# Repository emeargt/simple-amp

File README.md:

# simple-amp
This repository contains a KiCad project for a simple guitar bridge amplifier.

The board is designed to fit in a stomp box with panel mount switches.

## Schematic

## Board Layout
Top | Bottom
:---: | :---:
 | 

## Changelog

### v01
* Initial schematic and board layout

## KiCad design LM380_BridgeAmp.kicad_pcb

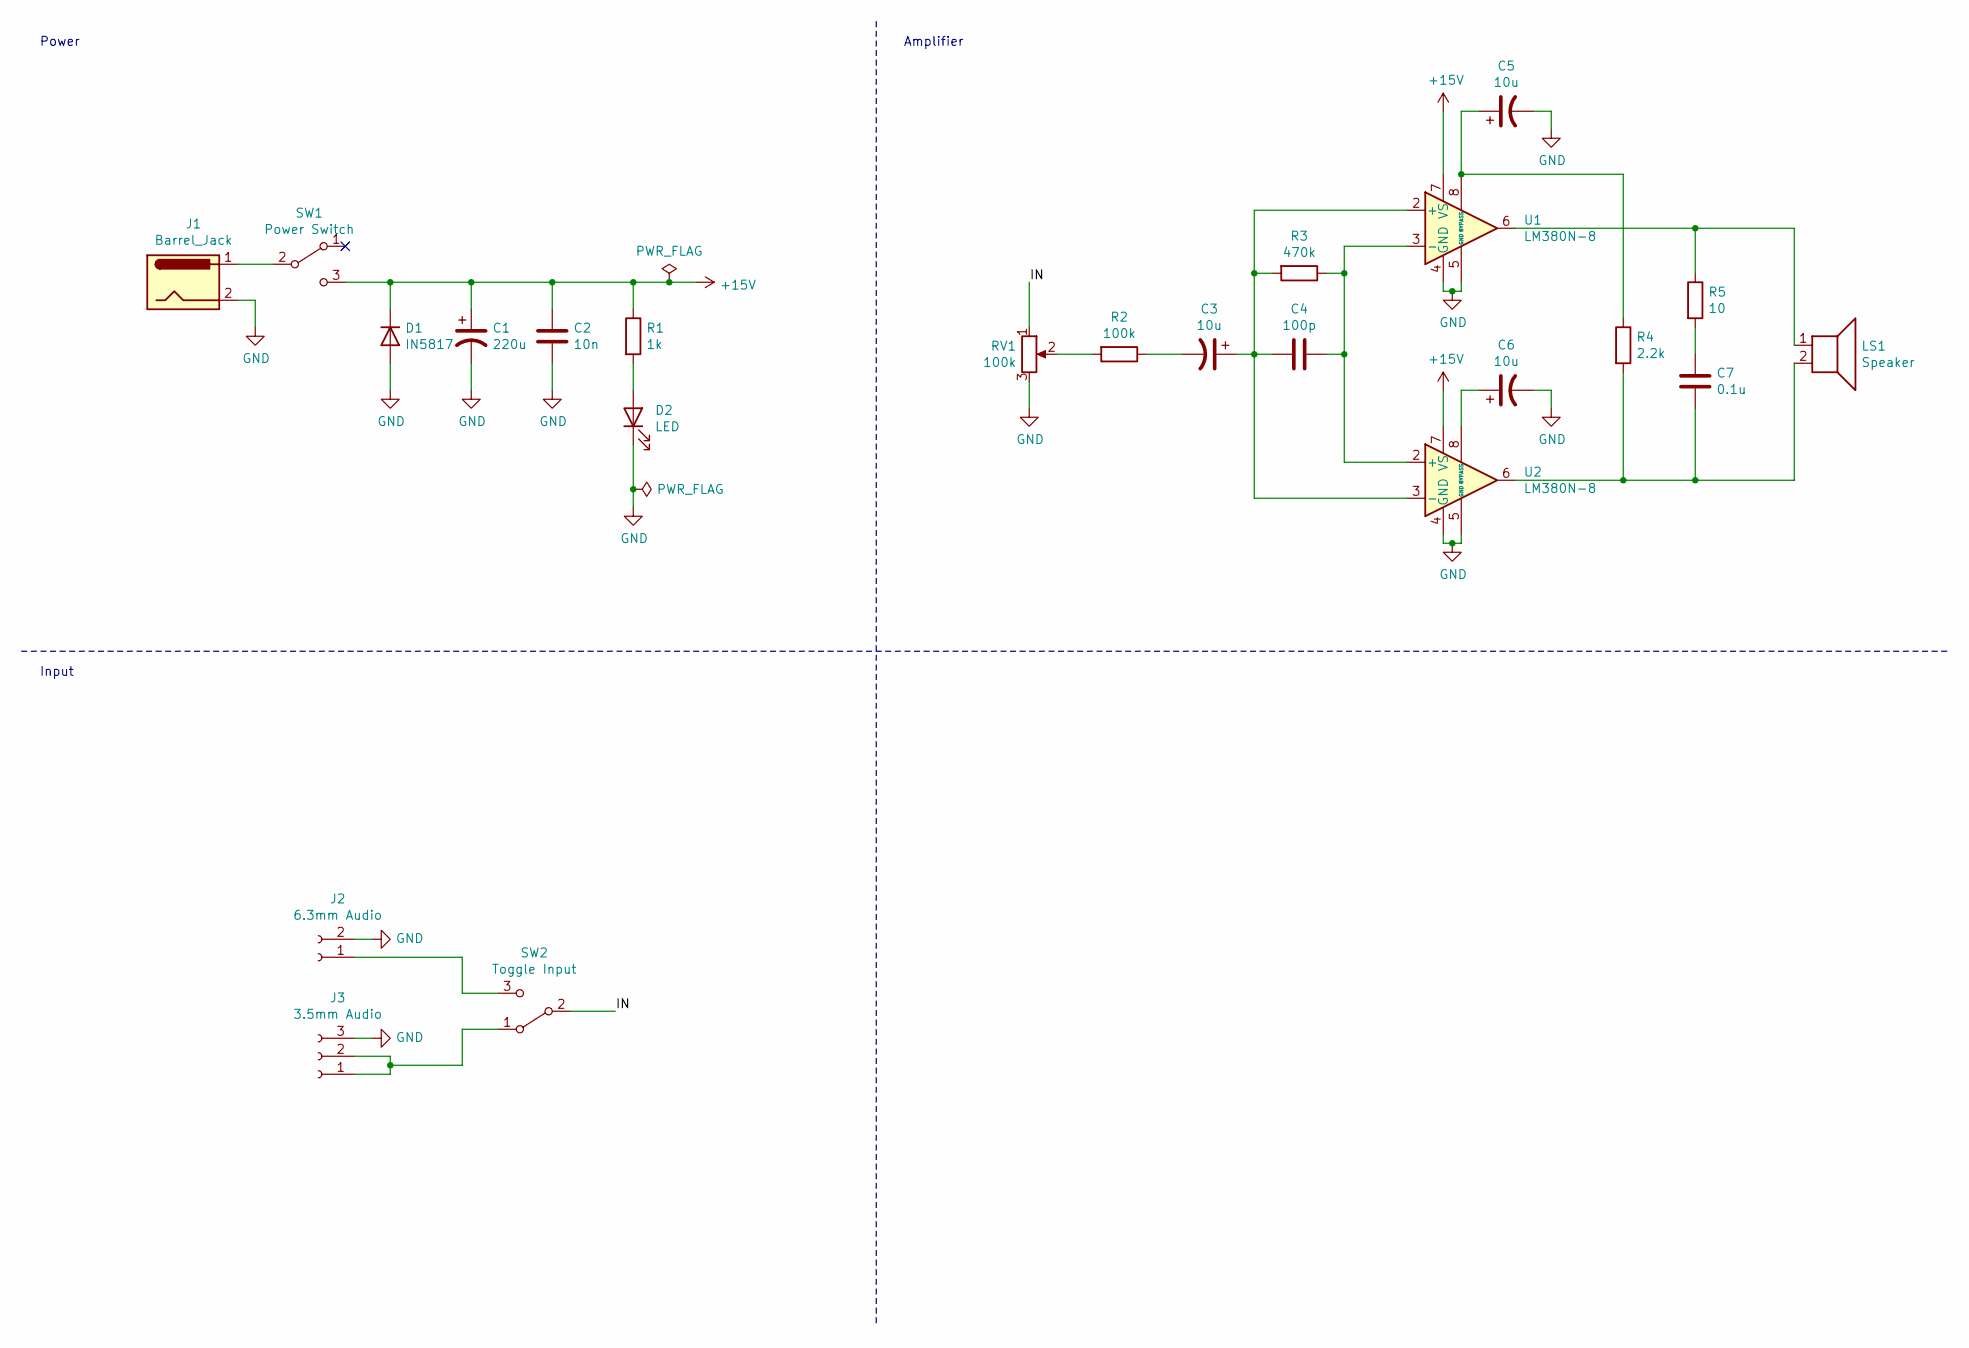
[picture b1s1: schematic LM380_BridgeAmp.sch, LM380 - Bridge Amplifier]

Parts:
C1: 220u; CP_Radial_D6.3mm_P2.50mm
C2: 10n; C_Disc_D5.0mm_W2.5mm_P2.50mm
C3, C5, C6: 10u; CP_Radial_D5.0mm_P2.00mm
C4: 100p; C_Disc_D5.0mm_W2.5mm_P5.00mm
C7: 0.1u; C_Axial_L5.1mm_D3.1mm_P10.00mm_Horizontal
D1: IN5817; D_DO-41_SOD81_P10.16mm_Horizontal
D2: LED; LED_D5.0mm_Clear
J1: Barrel_Jack; SolderWire-0.25sqmm_1x02_P4.2mm_D0.65mm_OD1.7mm
J2: 6.3mm Audio; SolderWire-0.25sqmm_1x02_P4.2mm_D0.65mm_OD1.7mm
J3: 3.5mm Audio; SolderWire-0.25sqmm_1x03_P4.2mm_D0.65mm_OD1.7mm
LS1: Speaker; SolderWire-0.25sqmm_1x02_P4.2mm_D0.65mm_OD1.7mm
R1: 1k; R_Axial_DIN0207_L6.3mm_D2.5mm_P7.62mm_Horizontal
R2: 100k; R_Axial_DIN0207_L6.3mm_D2.5mm_P7.62mm_Horizontal
R3: 470k; R_Axial_DIN0207_L6.3mm_D2.5mm_P7.62mm_Horizontal
R4: 2.2k; R_Axial_DIN0207_L6.3mm_D2.5mm_P7.62mm_Horizontal
R5: 10; R_Axial_DIN0207_L6.3mm_D2.5mm_P7.62mm_Horizontal
RV1: 100k; Potentiometer_TT_P0915N
SW1: Power Switch; Toggle_Switch_100SP1T1B4M2QE
SW2: Toggle Input; Toggle_Switch_100SP1T1B4M2QE
U1, U2: LM380N-8; DIP-8_W7.62mm

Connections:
+15V: C1.1, C2.1, D1.1 (K), R1.1, SW1.3 (C), U1.7 (VS), U2.7 (VS)
/IN: RV1.1, SW2.2 (B)
GND: C1.2, C2.2, C5.2, C6.2, D1.2 (A), D2.1 (K), J1.2, J2.2, J3.3, RV1.3, U1.4 (GND), U1.5 (GND), U2.4 (GND), U2.5 (GND)
unnamed: C3.1, C4.2, R3.2, U1.2 (+), U2.3 (-)
unnamed: C3.2, R2.1
unnamed: C4.1, R3.1, U1.3 (-), U2.2 (+)
unnamed: C5.1, R4.1, U1.8 (BYPASS)
unnamed: C6.1, U2.8 (BYPASS)
unnamed: C7.1, R5.2
unnamed: C7.2, LS1.2, R4.2, U2.6
unnamed: D2.2 (A), R1.2
unnamed: J1.1, SW1.2 (B)
unnamed: J2.1, SW2.3 (C)
unnamed: J3.1, J3.2, SW2.1 (A)
unnamed: LS1.1, R5.1, U1.6
unnamed: R2.2, RV1.2

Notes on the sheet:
Input
Power
Amplifier

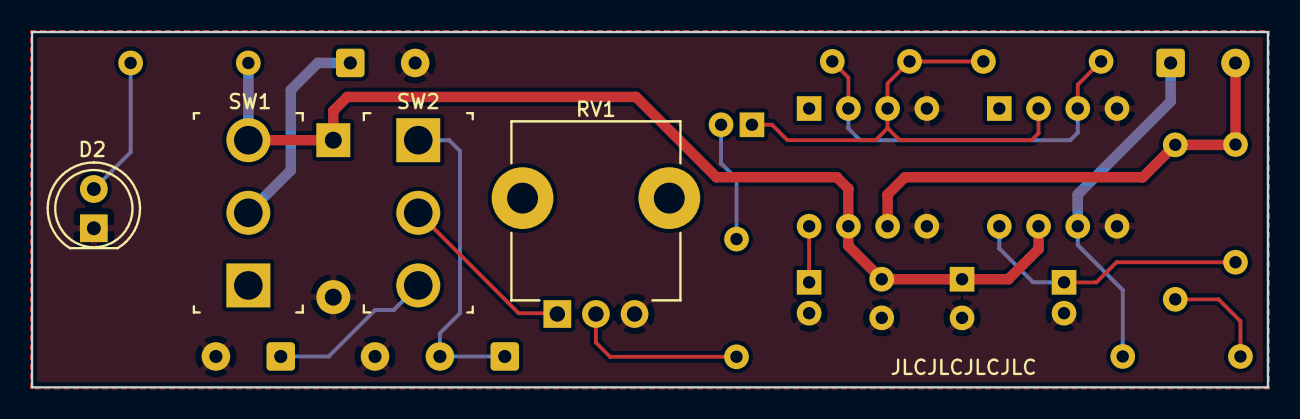
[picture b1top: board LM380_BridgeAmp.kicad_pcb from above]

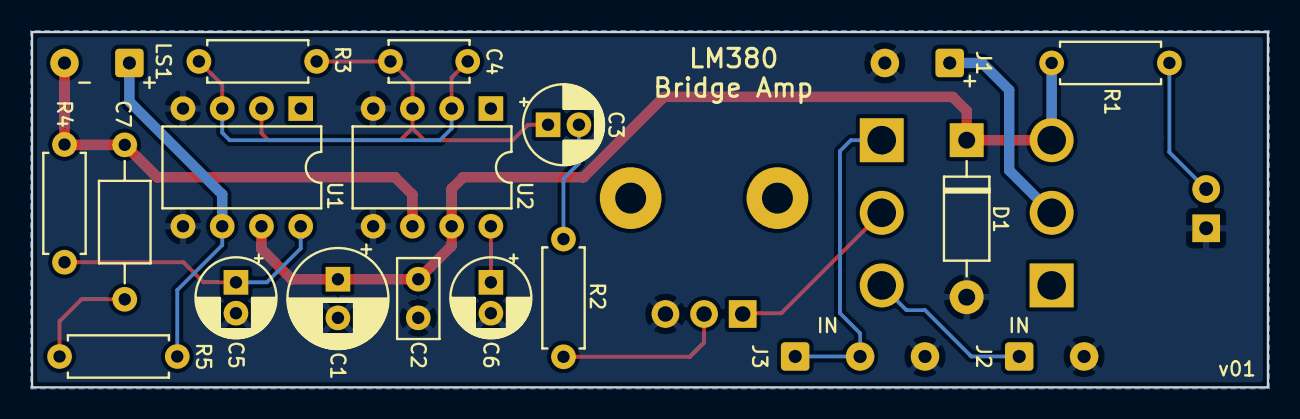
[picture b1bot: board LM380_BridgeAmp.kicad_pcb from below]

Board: 2 copper layers, 80.0 x 23.0 mm, 23 parts (19 on the bottom side), 16 nets.

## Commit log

2021-12-23 Add schematic and board images
2022-04-26 Remove header from readme
